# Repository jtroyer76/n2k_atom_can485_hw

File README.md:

# n2k_atom_can485_hw

A carrier board for the Seeed Studio XIAO ESP32-S3 that puts NMEA 2000 (CAN) and RS485/RS422 on one board, with a 3D-printed enclosure. It is powered from the NMEA 2000 drop, so one cable carries power and data. Made for gateways between NMEA 0183 devices on RS422 (for example an AIS transponder) and an NMEA 2000 network. (The name is from a first plan built on the M5Stack ATOM.)

Status: v0.1 ordered (JLCPCB, partly assembled), not yet built or tested. [Schematic PDF](docs/n2k_atom_can485-schematic.pdf), KiCad 10 project in `kicad/`, Gerbers, BOM and placement files for JLCPCB in `fab/`, 3D-printed enclosure (OpenSCAD, not yet printed) in [`enclosure/`](enclosure/README.md).

| Top | Bottom |
|---|---|
|  |  | Design and open questions: [docs/SPEC.md](docs/SPEC.md).

## Planned features

- NMEA 2000 / CAN transceiver (±58 V bus pins), 3.3 V logic, on the ESP32-S3's TWAI controller.
- Isolated RS485/RS422 transceiver, so the RS422 device's ground stays separate from the NMEA 2000 network ground.
- 12 V NMEA 2000 network power → 5 V for the XIAO, with reverse-polarity, overcurrent and surge protection.
- Optional 120 Ω termination on each bus, off by default: close solder jumper JP1 (CAN, next to the CAN transceiver) or JP2 (RS485, beside the RS485 chip).
- One pluggable terminal block: NET-S, NET-C, CAN-H, CAN-L, RS485 A, RS485 B, RS485 isolated GND.
- 32 × 64 mm, 2 layers. Built at JLCPCB with SMT assembly.

## Pins (XIAO ESP32-S3)

| Function | Pin | GPIO |
|---|---|---|
| CAN TX / RX | D8 / D9 | 7 / 8 |
| RS485 TX / RX / DE | D0 / D1 / D3 | 1 / 2 / 4 |

## License

CERN-OHL-S-2.0. See [LICENSE](LICENSE).

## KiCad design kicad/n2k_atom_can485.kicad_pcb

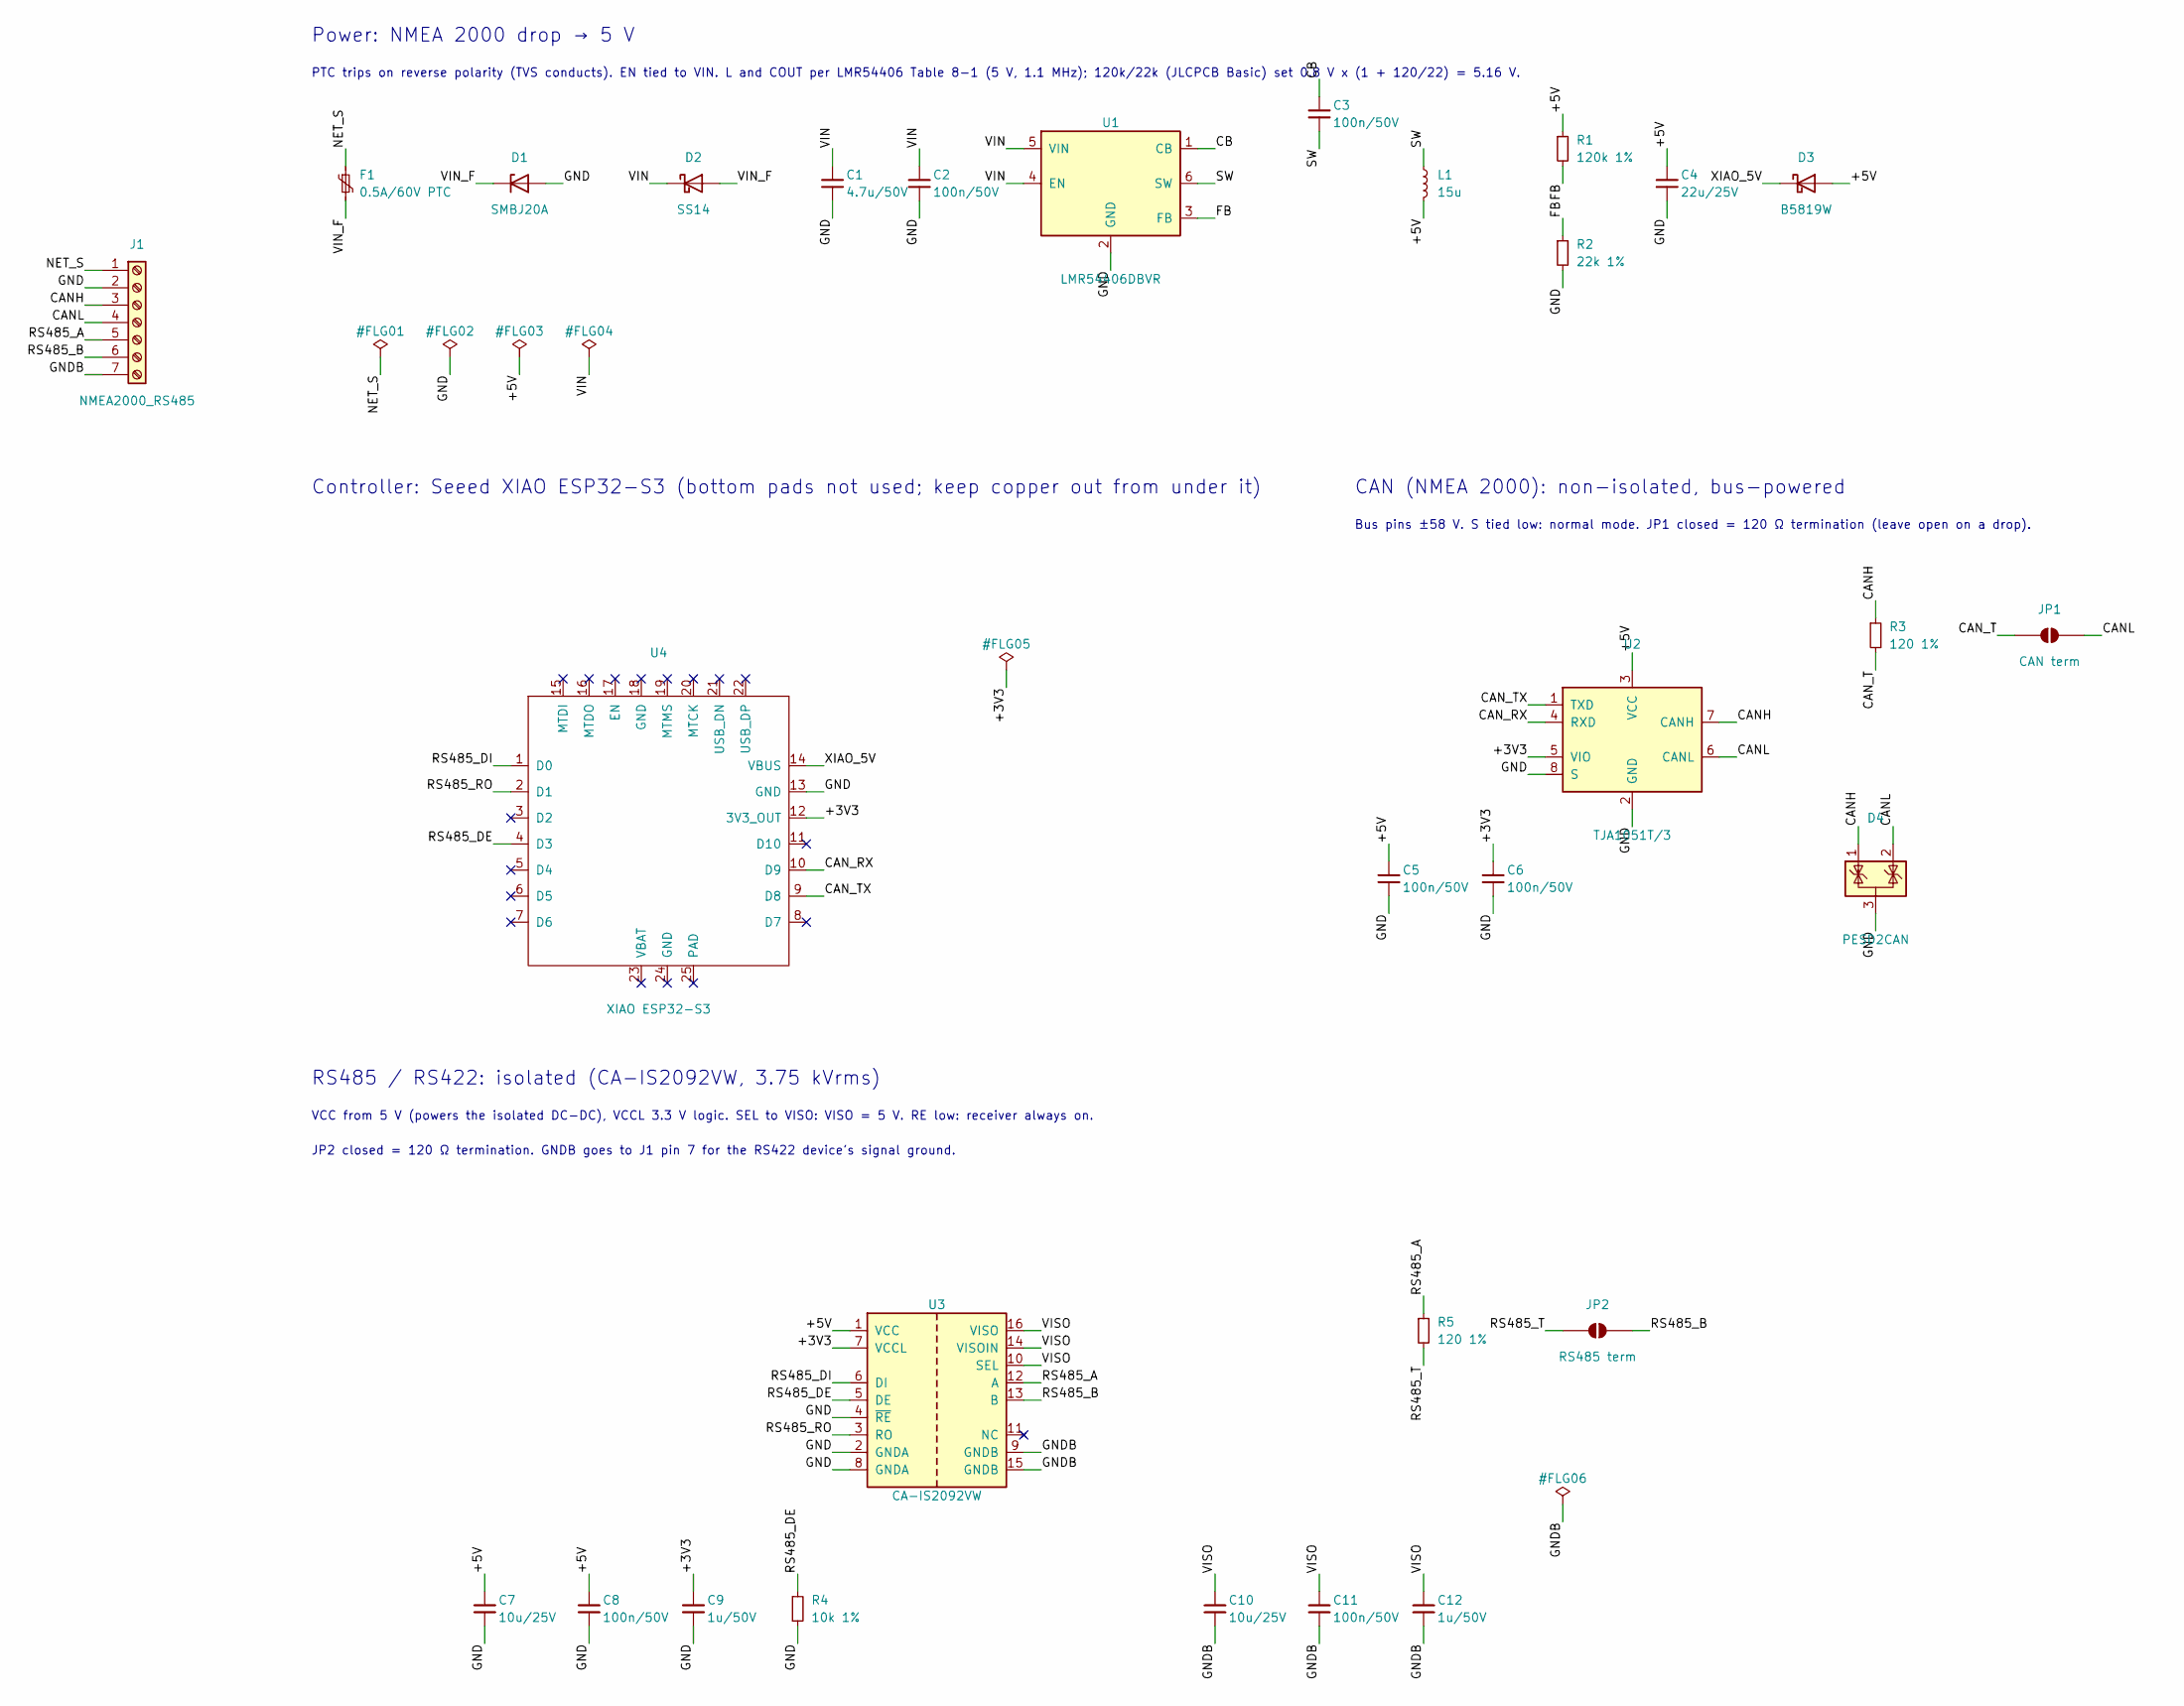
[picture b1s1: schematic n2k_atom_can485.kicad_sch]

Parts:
C1: 4.7u/50V; C_1206_3216Metric; LCSC C29823
C2, C3, C5, C6, C8, C11: 100n/50V; C_0603_1608Metric; LCSC C14663
C4: 22u/25V; C_0805_2012Metric; LCSC C45783
C7, C10: 10u/25V; C_0805_2012Metric; LCSC C15850
C9, C12: 1u/50V; C_0603_1608Metric; LCSC C15849
D1: SMBJ20A; D_SMB; MPN SMBJ20A (unidirectional TVS); LCSC C19077575
D2: SS14; D_SMA; MPN SS14 (reverse polarity); LCSC C2480
D3: B5819W; D_SOD-123; MPN B5819W; LCSC C8598
D4: PESD2CAN; SOT-23; MPN PESD2CAN,215; LCSC C75176
F1: 0.5A/60V PTC; Fuse_1812_4532Metric; MPN BSMD1812-050-60V; LCSC C883142
J1: NMEA2000_RS485; MX15EDGRC-3.5-07P; MPN MAX MX15EDGRC-3.5-07P-GN01-Cu-A; LCSC C5188300
JP1: CAN term; SolderJumper-2_P1.3mm_Open_RoundedPad1.0x1.5mm
JP2: RS485 term; SolderJumper-2_P1.3mm_Open_RoundedPad1.0x1.5mm
L1: 15u; L_Sunlord_SWPA5040S; MPN SWPA5040S150MT; LCSC C44888
R1: 120k 1%; R_0603_1608Metric; LCSC C25808
R2: 22k 1%; R_0603_1608Metric; LCSC C31850
R3, R5: 120 1%; R_0603_1608Metric; LCSC C22787
R4: 10k 1%; R_0603_1608Metric; LCSC C25804
U1: LMR54406DBVR; SOT-23-6; MPN LMR54406DBVR; LCSC C5219316
U2: TJA1051T/3; SOIC-8_3.9x4.9mm_P1.27mm; MPN TJA1051T/3/1J; LCSC C38695
U3: CA-IS2092VW; SOIC-16W_7.5x10.3mm_P1.27mm; MPN CA-IS2092VW; LCSC C7422559
U4: XIAO ESP32-S3; XIAO-ESP32-S3-SMD-HandSolder; MPN Seeed 113991114; LCSC C20467913

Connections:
/+3V3: C6.1, C9.1, U2.5 (VIO), U3.7 (VCCL), U4.12 (3V3_OUT)
/+5V: C4.1, C5.1, C7.1, C8.1, D3.2 (A), L1.2, R1.1, U2.3 (VCC), U3.1 (VCC)
/CANH: D4.1 (K), J1.3, R3.1, U2.7 (CANH)
/CANL: D4.2 (K), J1.4, JP1.2 (B), U2.6 (CANL)
/CAN_RX: U2.4 (RXD), U4.10 (D9)
/CAN_T: JP1.1 (A), R3.2
/CAN_TX: U2.1 (TXD), U4.9 (D8)
/CB: C3.1, U1.1 (CB)
/FB: R1.2, R2.1, U1.3 (FB)
/GND: C1.2, C2.2, C4.2, C5.2, C6.2, C7.2, C8.2, C9.2, D1.2 (A), D4.3 (A), J1.2, R2.2, R4.2, U1.2 (GND), U2.2 (GND), U2.8 (S), U3.2 (GNDA), U3.4 (~RE), U3.8 (GNDA), U4.13 (GND)
/GNDB: C10.2, C11.2, C12.2, J1.7, U3.9 (GNDB), U3.15 (GNDB)
/NET_S: F1.1, J1.1
/RS485_A: J1.5, R5.1, U3.12 (A)
/RS485_B: J1.6, JP2.2 (B), U3.13 (B)
/RS485_DE: R4.1, U3.5 (DE), U4.4 (D3)
/RS485_DI: U3.6 (DI), U4.1 (D0)
/RS485_RO: U3.3 (RO), U4.2 (D1)
/RS485_T: JP2.1 (A), R5.2
/SW: C3.2, L1.1, U1.6 (SW)
/VIN: C1.1, C2.1, D2.1 (K), U1.4 (EN), U1.5 (VIN)
/VIN_F: D1.1 (K), D2.2 (A), F1.2
/VISO: C10.1, C11.1, C12.1, U3.10 (SEL), U3.14 (VISOIN), U3.16 (VISO)
/XIAO_5V: D3.1 (K), U4.14 (VBUS)

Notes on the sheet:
Power: NMEA 2000 drop → 5 V
PTC trips on reverse polarity (TVS conducts). EN tied to VIN. L and COUT per LMR54406 Table 8-1 (5 V, 1.1 MHz); 120k/22k (JLCPCB Basic) set 0.8 V x (1 + 120/22) = 5.16 V.
Controller: Seeed XIAO ESP32-S3 (bottom pads not used; keep copper out from under it)
CAN (NMEA 2000): non-isolated, bus-powered
Bus pins ±58 V. S tied low: normal mode. JP1 closed = 120 Ω termination (leave open on a drop).
RS485 / RS422: isolated (CA-IS2092VW, 3.75 kVrms)
VCC from 5 V (powers the isolated DC-DC), VCCL 3.3 V logic. SEL to VISO: VISO = 5 V. RE low: receiver always on.
JP2 closed = 120 Ω termination. GNDB goes to J1 pin 7 for the RS422 device's signal ground.

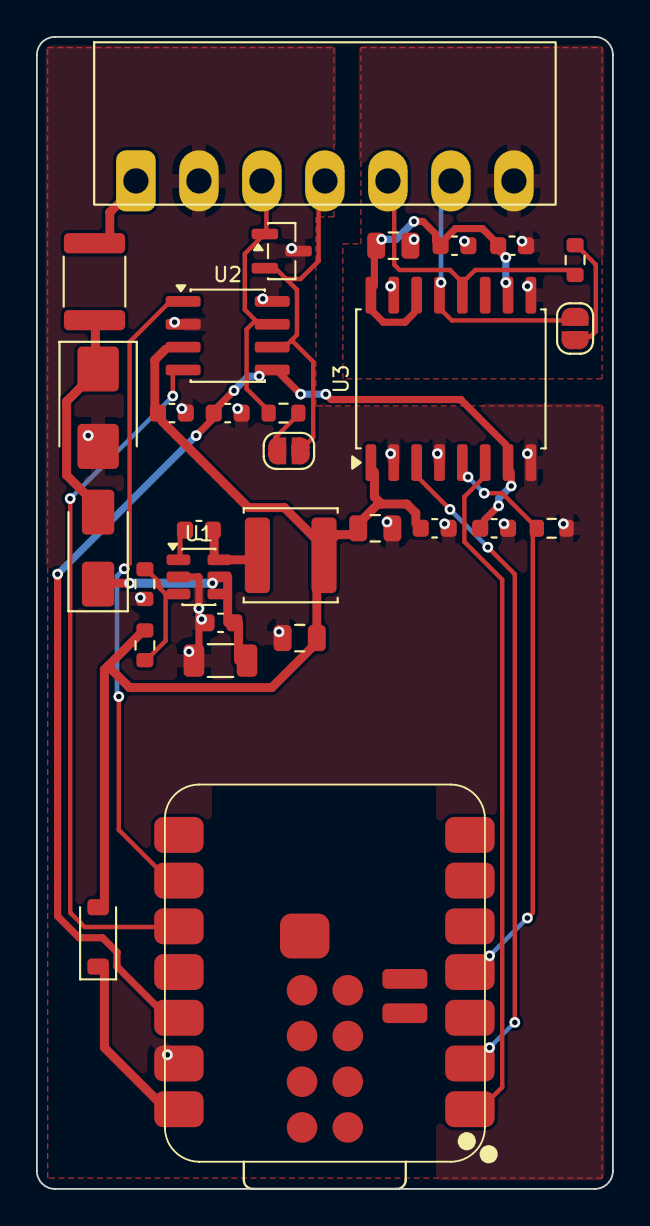
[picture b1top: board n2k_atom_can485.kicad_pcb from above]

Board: 2 copper layers, 32.0 x 64.0 mm, 30 parts (0 on the bottom side), 23 nets.

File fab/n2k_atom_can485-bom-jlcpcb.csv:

Comment,Designator,Footprint,LCSC Part #
4.7u/50V,C1,C_1206_3216Metric,C29823
100n/50V,"C2,C3,C5,C6,C8,C11",C_0603_1608Metric,C14663
22u/25V,C4,C_0805_2012Metric,C45783
10u/25V,"C7,C10",C_0805_2012Metric,C15850
1u/50V,"C9,C12",C_0603_1608Metric,C15849
SMBJ20A,D1,D_SMB,C19077575
SS14,D2,D_SMA,C2480
B5819W,D3,D_SOD-123,C8598
PESD2CAN,D4,SOT-23,C75176
0.5A/60V PTC,F1,Fuse_1812_4532Metric,C883142
15u,L1,L_Sunlord_SWPA5040S,C44888
120k 1%,R1,R_0603_1608Metric,C25808
22k 1%,R2,R_0603_1608Metric,C31850
120 1%,"R3,R5",R_0603_1608Metric,C22787
10k 1%,R4,R_0603_1608Metric,C25804
LMR54406DBVR,U1,SOT-23-6,C5219316
TJA1051T/3,U2,SOIC-8_3.9x4.9mm_P1.27mm,C38695
CA-IS2092VW,U3,SOIC-16W_7.5x10.3mm_P1.27mm,C7422559
